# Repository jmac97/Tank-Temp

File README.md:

# Tank-Temp

I wanted to make another version of my previous Aquarium Bot project due to the WiFi issues and also wanted a project to get comfortable with the STM32 microcontroller. I developed the system with an STM32 development board and created a "hat" that monitored the temperature, displayed the information on an OLED screen, and alerted my friend via an LED. Detailed description [here](https://www.juliesongmceldoon.com/tank-temp).

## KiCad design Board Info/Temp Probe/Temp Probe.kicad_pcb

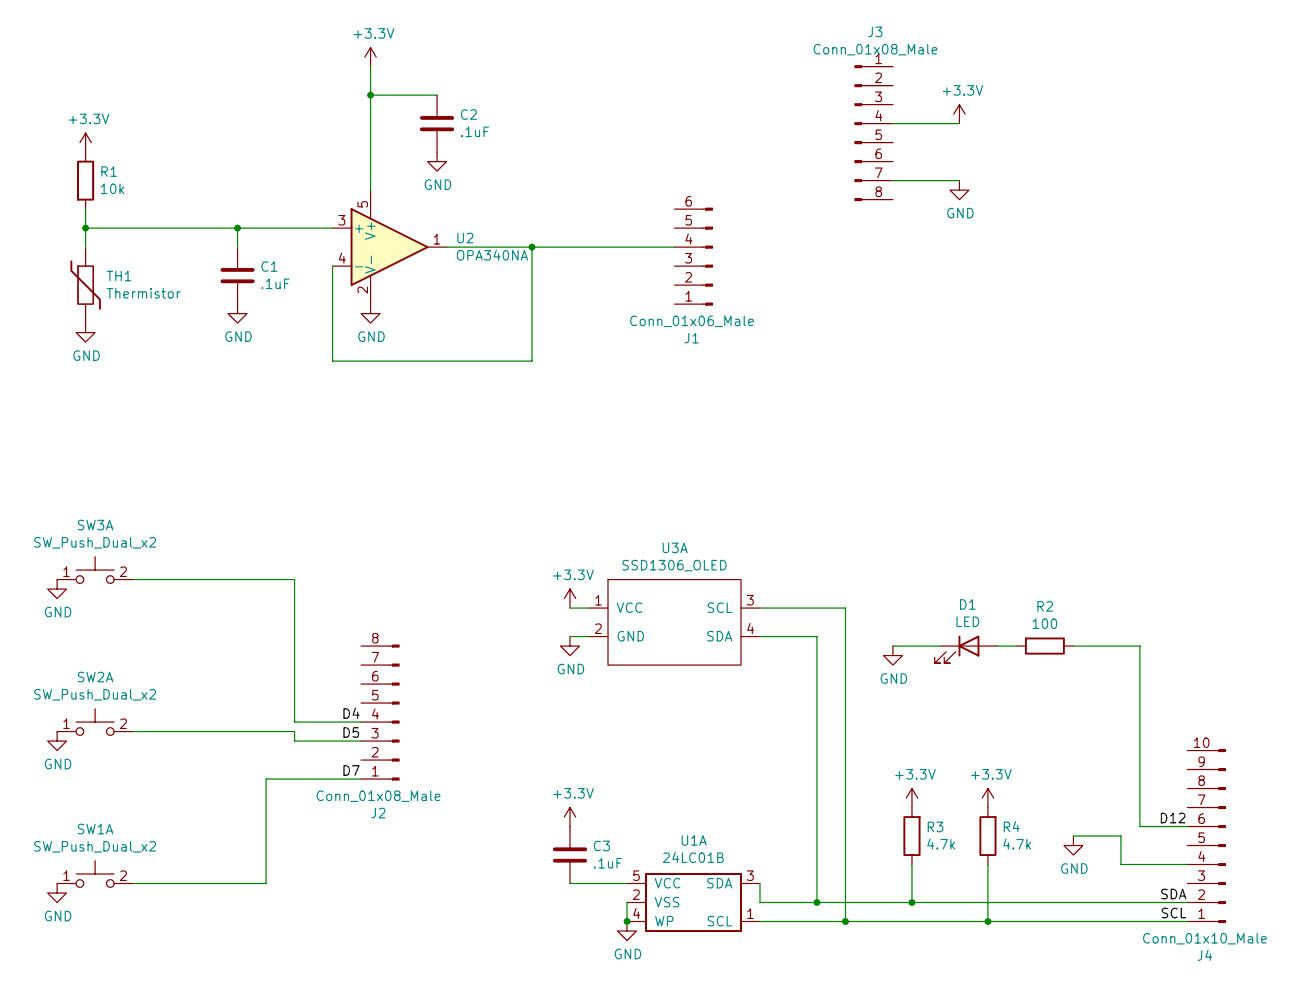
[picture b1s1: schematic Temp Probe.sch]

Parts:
C1, C2, C3: .1uF; C_0805_2012Metric
D1: LED; PinSocket_1x02_P2.54mm_Vertical
J1: Conn_01x06_Male; PinHeader_1x06_P2.54mm_Vertical
J2, J3: Conn_01x08_Male; PinHeader_1x08_P2.54mm_Vertical
J4: Conn_01x10_Male; PinHeader_1x10_P2.54mm_Vertical
R1: 10k; R_0805_2012Metric_Pad1.20x1.40mm_HandSolder
R2: 100; R_0805_2012Metric
R3, R4: 4.7k; R_0805_2012Metric
SW1, SW2, SW3: SW_Push_Dual_x2; SW_PUSH_6mm_H5mm
TH1: Thermistor; TerminalBlock_Phoenix_MPT-0,5-2-2.54_1x02_P2.54mm_Horizontal
U1: 24LC01B; SOT-23-5
U2: OPA340NA; SOT-23-5
U3: SSD1306_OLED; PinSocket_1x04_P2.54mm_Vertical

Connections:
+3V3: C2.1, C3.1, J3.4, R1.1, R3.2, R4.2, U2.5 (V+), U3.1 (VCC)
/D4: J2.4, SW3.2 (D)
/D5: J2.3, SW2.2 (D)
/D7: J2.1, SW1.2 (D)
/D12: J4.6, R2.1
/SCL: J4.1, R4.1, U1.1 (SCL), U3.3 (SCL)
/SDA: J4.2, R3.1, U1.3 (SDA), U3.4 (SDA)
GND: C1.2, C2.2, D1.1 (K), J3.7, J4.4, SW1.1 (C), SW2.1 (C), SW3.1 (C), TH1.2, U1.2 (VSS), U1.4 (WP), U2.2 (V-), U3.2 (GND)
unnamed: C1.1, R1.2, TH1.1, U2.3 (+)
unnamed: C3.2, U1.5 (VCC)
unnamed: D1.2 (A), R2.2
unnamed: J1.4, U2.1, U2.4 (-)

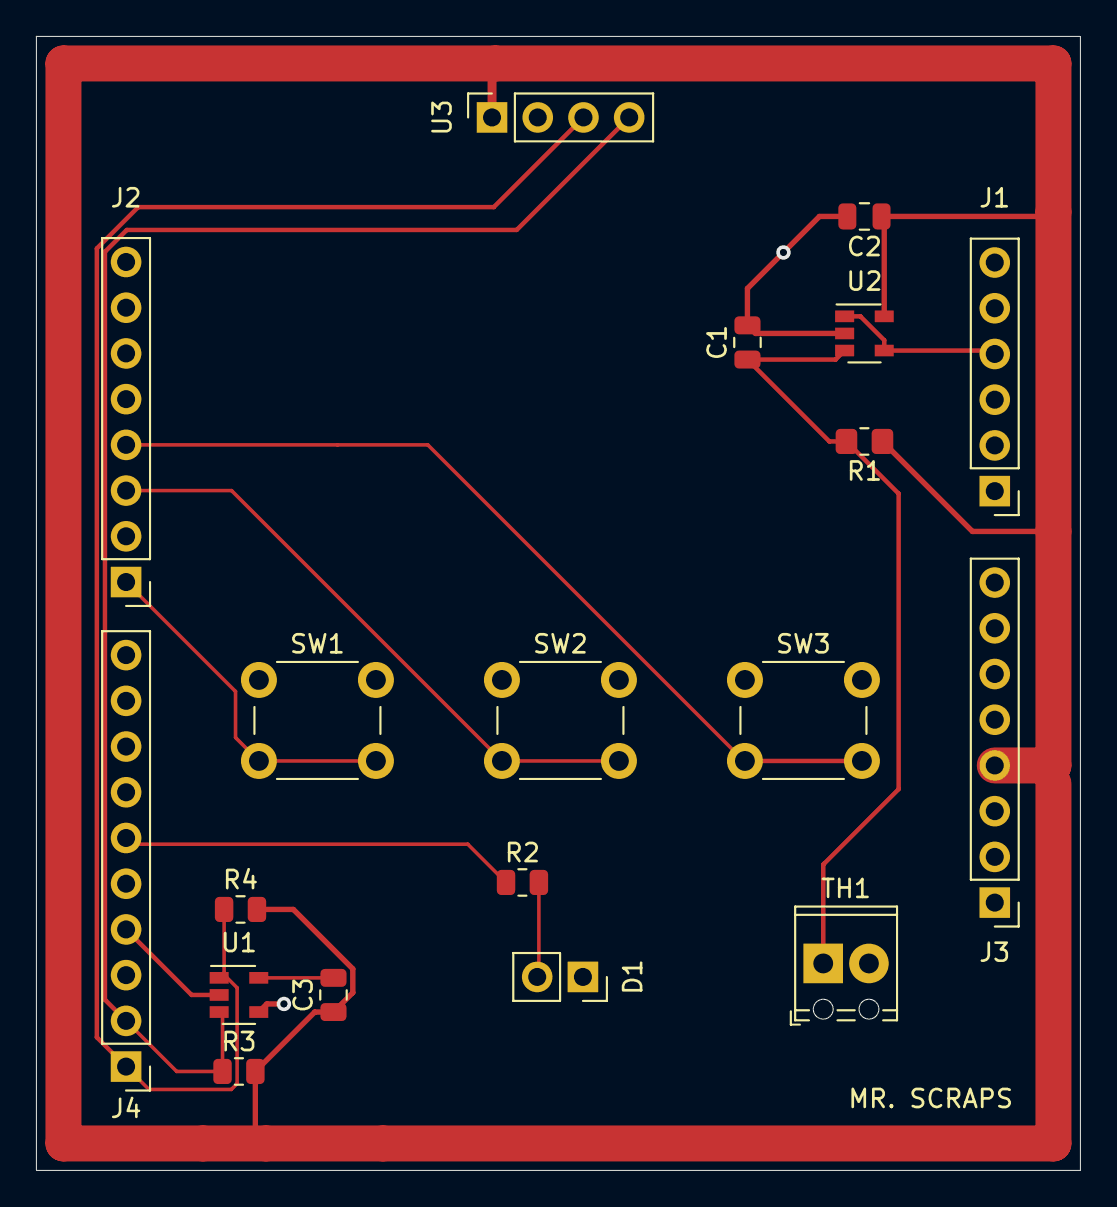
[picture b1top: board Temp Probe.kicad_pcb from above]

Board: 2 copper layers, 58.0 x 63.0 mm, 19 parts (0 on the bottom side), 12 nets.

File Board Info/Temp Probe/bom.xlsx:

Ref Des | Part Number | Value
C1, C2, C3 |  | .1 uF
D1 | have | Red LED
J1 | have | Connector Pinheader 2.54mm 1x6 Male
J2, J3 | have | Connector Pinheader 2.54mm 1x8 Male
J4 | have | Connector Pinheader 2.54mm 1x10 Male
R1 |  | 10k
R2 |  | 100
R3, R4 |  | 4.7K
SW1A, SW2A, SW3A | have | Tactile switch
TH1 | have | Thermistor
U1A | 24LC01B | I2C EEPROM
U2 | OPA340NA | Op amp
U3A | have_SSD1306 | OLED driver and display

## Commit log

2020-10-13 put on github
2020-11-11 board and schematic
2020-11-12 gerber and drill info
2020-11-21 BOARD STUFF
2020-12-09 oh my god
2021-01-17 eeprom test
2022-07-20 pic from portfolio
